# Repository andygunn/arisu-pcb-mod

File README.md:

# Arisu Keyboard PCB with Modifications
アリス PCB designed using KiCad. The layout was originally created by FateNozomi, inspired by Lyn's EM7 and TGR Alice with some modification.

Key differences of the original PCB:
- Removed the extra [B] key on the right half and shifted the [NM,.?] row to the left by 0.25U.
- Shifted the 3 keys to the right and added arrow keys.
- Tweaked the bottom so that the 1.5U keys doesn't protrude out a little.

Additional modifications to the file include:
- Addition of stepped capslock position.
- Addition of full backspace position, connected to switch 59 (row 0, column 13).
- Replacing the mini-USB connector with USB-C.
- Shifting the USB-C connector vertically, to reduce the distance to the edge of a case.

(Note: The modifications for full backspace and stepped capslock require a modification to the plate file to use.)

Shifting the [NM,.?] row to the left by 0.25U required quite some work on the arrangement of keys for the right half.
As a result, this does not give the same typing experience as Lyn's EM7 and TGR Alice.
Lyn's EM7 and TGR Alice uses the home row as the center point to vertically align both halves while I used the number row instead.
Due to the nature of staggered keyboards, aligning using the number row resulted in the home row not being aligned.

Disclaimer: Use these files at your own risk.

## Gerber Files
Download the gerber files under [releases](https://github.com/andygunn/arisu-pcb-mod/releases).

## Assembly
For the components required, you may refer to the bill of materials included along with the release as reference or load up the design file in KiCad.
All the components can be soldered using a regular soldering iron, though soldering the Micro USB receptacle might be the biggest hurdle.

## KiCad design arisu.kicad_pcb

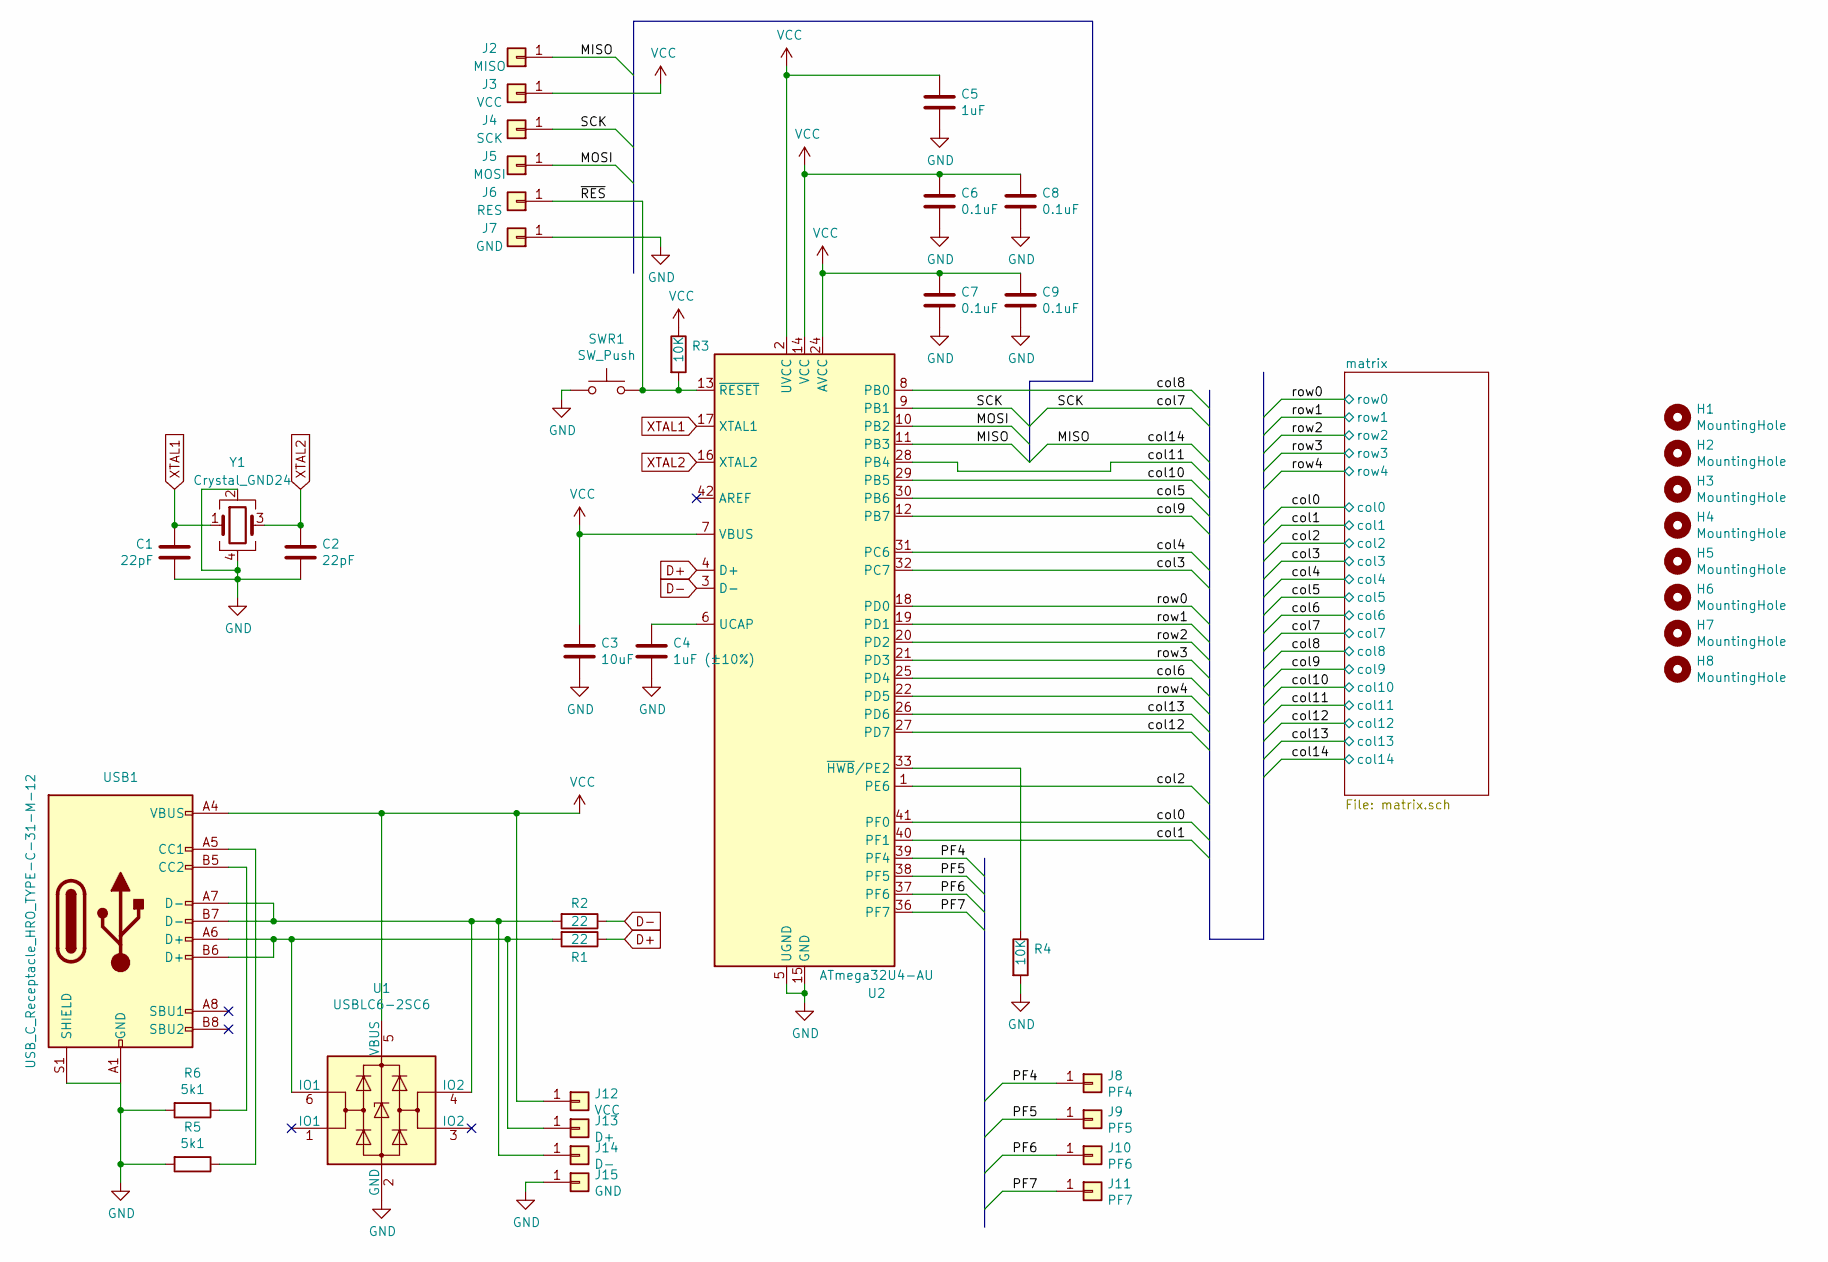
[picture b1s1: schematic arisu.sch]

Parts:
C1, C2: 22pF; C_0805_HandSoldering; LCSC C1804
C3: 10uF; C_0805_HandSoldering; LCSC C15850
C4: 1uF (±10%); C_0805_HandSoldering; LCSC C28323
C5: 1uF; C_0805_HandSoldering; LCSC C28323
C6, C7, C8, C9: 0.1uF; C_0805_HandSoldering; LCSC C28233
H1, H2, H3, H4, H5, H6, H7, H8: MountingHole; MountingHole_2.2mm_M2_Pad
J2: MISO; Pin_Header_Straight_1x01_Pitch2.54mm
J3, J12: VCC; Pin_Header_Straight_1x01_Pitch2.54mm
J4: SCK; Pin_Header_Straight_1x01_Pitch2.54mm
J5: MOSI; Pin_Header_Straight_1x01_Pitch2.54mm
J6: RES; Pin_Header_Straight_1x01_Pitch2.54mm
J7, J15: GND; Pin_Header_Straight_1x01_Pitch2.54mm
J8: PF4; Pin_Header_Straight_1x01_Pitch2.54mm
J9: PF5; Pin_Header_Straight_1x01_Pitch2.54mm
J10: PF6; Pin_Header_Straight_1x01_Pitch2.54mm
J11: PF7; Pin_Header_Straight_1x01_Pitch2.54mm
J13: D+; Pin_Header_Straight_1x01_Pitch2.54mm
J14: D-; Pin_Header_Straight_1x01_Pitch2.54mm
R1, R2: 22; R_0805_HandSoldering; LCSC C17561
R3, R4: 10K; R_0805_HandSoldering; LCSC C17414
R5, R6: 5k1; R_0805_2012Metric_Pad1.15x1.40mm_HandSolder; LCSC C27834
SWR1: SW_Push; SW_SPST_TL3342; LCSC C318884
U1: USBLC6-2SC6; SOT-23-6_Handsoldering; LCSC C7519
U2: ATmega32U4-AU; TQFP-44_10x10mm_P0.8mm; LCSC C44854
USB1: USB_C_Receptacle_HRO_TYPE-C-31-M-12
Y1: Crystal_GND24; Crystal_SMD_SeikoEpson_FA238-4pin_3.2x2.5mm_HandSoldering; LCSC C89371

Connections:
/MISO: J2.1, U2.11 (PB3); also elsewhere on the board
/MOSI: J5.1, U2.10 (PB2)
/PF4: J8.1, U2.39 (PF4)
/PF5: J9.1, U2.38 (PF5)
/PF6: J10.1, U2.37 (PF6)
/PF7: J11.1, U2.36 (PF7)
/SCK: J4.1, U2.9 (PB1); also elsewhere on the board
/col0: U2.41 (PF0); also elsewhere on the board
/col1: U2.40 (PF1); also elsewhere on the board
/col2: U2.1 (PE6); also elsewhere on the board
/col3: U2.32 (PC7); also elsewhere on the board
/col4: U2.31 (PC6); also elsewhere on the board
/col5: U2.30 (PB6); also elsewhere on the board
/col6: U2.25 (PD4); also elsewhere on the board
/col8: U2.8 (PB0); also elsewhere on the board
/col9: U2.12 (PB7); also elsewhere on the board
/col10: U2.29 (PB5); also elsewhere on the board
/col11: U2.28 (PB4); also elsewhere on the board
/col12: U2.27 (PD7); also elsewhere on the board
/col13: U2.26 (PD6); also elsewhere on the board
/row0: U2.18 (PD0); also elsewhere on the board
/row1: U2.19 (PD1); also elsewhere on the board
/row2: U2.20 (PD2); also elsewhere on the board
/row3: U2.21 (PD3); also elsewhere on the board
/row4: U2.22 (PD5); also elsewhere on the board
/~RES~: J6.1, R3.2, SWR1.2, U2.13 (~RESET)
D+: R1.1, U2.4 (D+)
D-: R2.1, U2.3 (D-)
GND: C1.1, C2.2, C3.2, C4.2, C5.2, C6.2, C7.2, C8.2, C9.2, J7.1, J15.1, R4.2, R5.2, R6.2, SWR1.1, U1.2 (GND), U2.5 (UGND), U2.15 (GND), U2.23 (GND), U2.35 (GND), U2.43 (GND), USB1.A1 (GND), USB1.A12 (GND), USB1.S1 (SHIELD), Y1.2, Y1.4
unnamed: C4.1, U2.6 (UCAP)
unnamed: J13.1, R1.2, U1.6 (IO1), USB1.A6 (D+), USB1.B6 (D+)
unnamed: J14.1, R2.2, U1.4 (IO2), USB1.A7 (D-), USB1.B7 (D-)
unnamed: R4.1, U2.33 (~HWB~/PE2)
unnamed: R5.1, USB1.A5 (CC1)
unnamed: R6.1, USB1.B5 (CC2)
VCC: C3.1, C5.1, C6.1, C7.1, C8.1, C9.1, J3.1, J12.1, R3.1, U1.5 (VBUS), U2.2 (UVCC), U2.7 (VBUS), U2.14 (VCC), U2.24 (AVCC), U2.34 (VCC), U2.44 (AVCC), USB1.A4 (VBUS), USB1.A9 (VBUS)
XTAL1: C1.2, U2.17 (XTAL1), Y1.1
XTAL2: C2.1, U2.16 (XTAL2), Y1.3

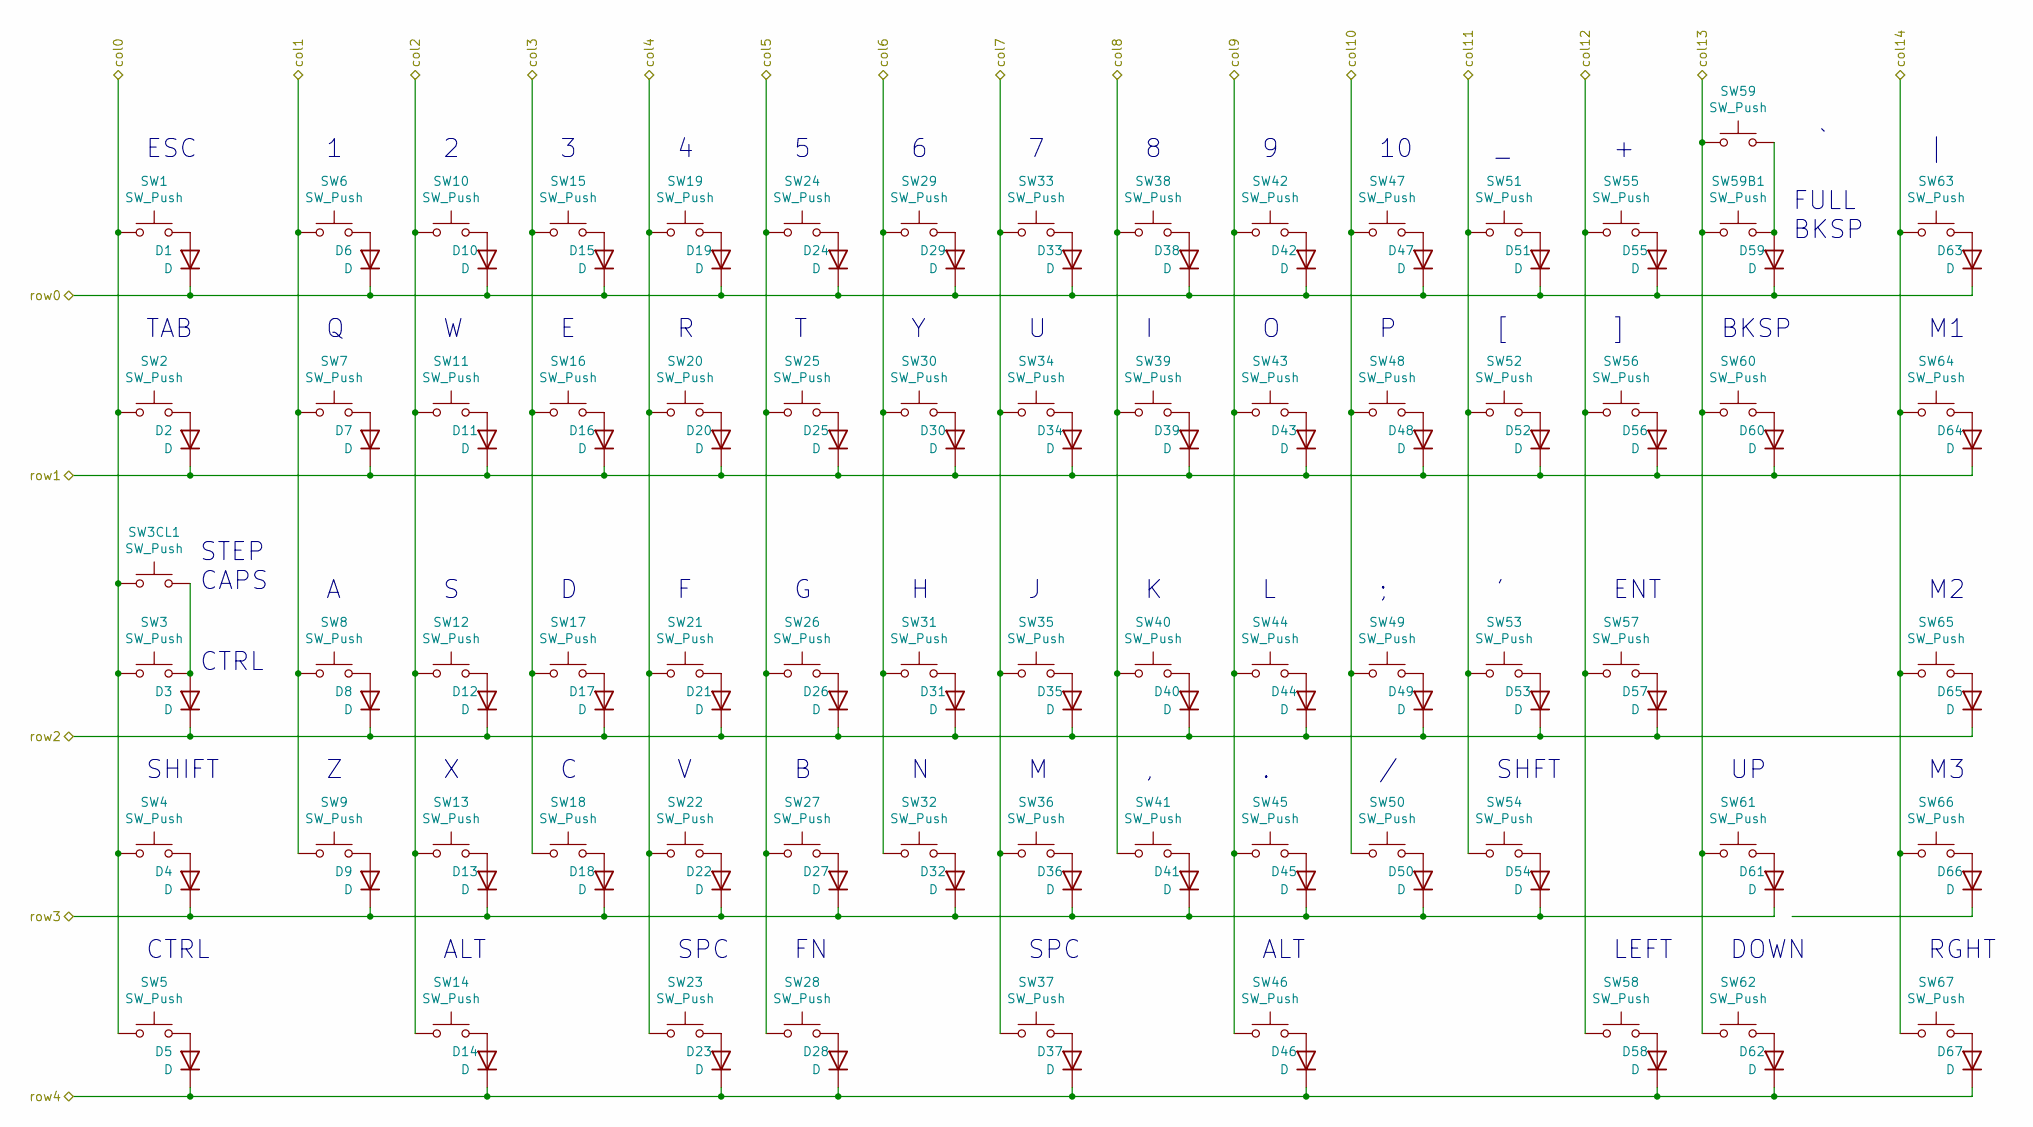
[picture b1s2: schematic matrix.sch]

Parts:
D1, D2, D3, D4, D5, D6, D7, D8, D9, D10, D11, D12, D13, D14, D15, D16, D17, D18, D19, D20, D21, D22, D23, D24, D25, D26, D27, D28, D29, D30, D31, D32, D33, D34, D35, D36, D37, D38, D39, D40, D41, D42, D43, D44, D45, D46, D47, D48, D49, D50, D51, D52, D53, D54, D55, D56, D57, D58, D59, D60, D61, D62, D63, D64, D65, D66, D67: D; D_SOD-123; LCSC C81598
SW1, SW6, SW7, SW8, SW9, SW10, SW11, SW12, SW13, SW15, SW16, SW17, SW18, SW19, SW20, SW21, SW22, SW24, SW25, SW26, SW27, SW28, SW29, SW30, SW31, SW32, SW33, SW34, SW35, SW36, SW38, SW39, SW40, SW41, SW42, SW43, SW44, SW45, SW47, SW48, SW49, SW50, SW51, SW52, SW53, SW55, SW56, SW58, SW59, SW61, SW62, SW63, SW64, SW65, SW66, SW67: SW_Push; SW_Cherry_MX_1.00u_PCB
SW2, SW5, SW14, SW46, SW60: SW_Push; SW_Cherry_MX_1.50u_PCB
SW3, SW54: SW_Push; SW_Cherry_MX_1.75u_PCB
SW3CL1: SW_Push; SW_Cherry_MX_1.25u_PCB
SW4: SW_Push; SW_Cherry_MX_2.25u_PCB
SW23: SW_Push; SW_Cherry_MX_2.00u_PCB_ReversedStabilizers
SW37: SW_Push; SW_Cherry_MX_2.75u_PCB_ReversedStabilizers
SW57: SW_Push; SW_Cherry_MX_2.25u_PCB_ReversedStabilizers
SW59B1: SW_Push; SW_Cherry_MX_2.00u_PCB

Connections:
/MISO: SW63.1, SW64.1, SW65.1, SW66.1, SW67.1; also elsewhere on the board
/SCK: SW33.1, SW34.1, SW35.1, SW36.1, SW37.1; also elsewhere on the board
/col0: SW1.1, SW2.1, SW3.1, SW3CL1.1, SW4.1, SW5.1; also elsewhere on the board
/col1: SW6.1, SW7.1, SW8.1, SW9.1; also elsewhere on the board
/col2: SW10.1, SW11.1, SW12.1, SW13.1, SW14.1; also elsewhere on the board
/col3: SW15.1, SW16.1, SW17.1, SW18.1; also elsewhere on the board
/col4: SW19.1, SW20.1, SW21.1, SW22.1, SW23.1; also elsewhere on the board
/col5: SW24.1, SW25.1, SW26.1, SW27.1, SW28.1; also elsewhere on the board
/col6: SW29.1, SW30.1, SW31.1, SW32.1; also elsewhere on the board
/col8: SW38.1, SW39.1, SW40.1, SW41.1; also elsewhere on the board
/col9: SW42.1, SW43.1, SW44.1, SW45.1, SW46.1; also elsewhere on the board
/col10: SW47.1, SW48.1, SW49.1, SW50.1; also elsewhere on the board
/col11: SW51.1, SW52.1, SW53.1, SW54.1; also elsewhere on the board
/col12: SW55.1, SW56.1, SW57.1, SW58.1; also elsewhere on the board
/col13: SW59.1, SW59B1.1, SW60.1, SW61.1, SW62.1; also elsewhere on the board
/row0: D1.1 (K), D6.1 (K), D10.1 (K), D15.1 (K), D19.1 (K), D24.1 (K), D29.1 (K), D33.1 (K), D38.1 (K), D42.1 (K), D47.1 (K), D51.1 (K), D55.1 (K), D59.1 (K), D63.1 (K); also elsewhere on the board
/row1: D2.1 (K), D7.1 (K), D11.1 (K), D16.1 (K), D20.1 (K), D25.1 (K), D30.1 (K), D34.1 (K), D39.1 (K), D43.1 (K), D48.1 (K), D52.1 (K), D56.1 (K), D60.1 (K), D64.1 (K); also elsewhere on the board
/row2: D3.1 (K), D8.1 (K), D12.1 (K), D17.1 (K), D21.1 (K), D26.1 (K), D31.1 (K), D35.1 (K), D40.1 (K), D44.1 (K), D49.1 (K), D53.1 (K), D57.1 (K), D65.1 (K); also elsewhere on the board
/row3: D4.1 (K), D9.1 (K), D13.1 (K), D18.1 (K), D22.1 (K), D27.1 (K), D32.1 (K), D36.1 (K), D41.1 (K), D45.1 (K), D50.1 (K), D54.1 (K), D61.1 (K); also elsewhere on the board
/row4: D5.1 (K), D14.1 (K), D23.1 (K), D28.1 (K), D37.1 (K), D46.1 (K), D58.1 (K), D62.1 (K), D67.1 (K); also elsewhere on the board
unnamed: D1.2 (A), SW1.2
unnamed: D2.2 (A), SW2.2
unnamed: D3.2 (A), SW3.2, SW3CL1.2
unnamed: D4.2 (A), SW4.2
unnamed: D5.2 (A), SW5.2
unnamed: D6.2 (A), SW6.2
unnamed: D7.2 (A), SW7.2
unnamed: D8.2 (A), SW8.2
unnamed: D9.2 (A), SW9.2
unnamed: D10.2 (A), SW10.2
unnamed: D11.2 (A), SW11.2
unnamed: D12.2 (A), SW12.2
unnamed: D13.2 (A), SW13.2
unnamed: D14.2 (A), SW14.2
unnamed: D15.2 (A), SW15.2
unnamed: D16.2 (A), SW16.2
unnamed: D17.2 (A), SW17.2
unnamed: D18.2 (A), SW18.2
unnamed: D19.2 (A), SW19.2
unnamed: D20.2 (A), SW20.2
unnamed: D21.2 (A), SW21.2
unnamed: D22.2 (A), SW22.2
unnamed: D23.2 (A), SW23.2
unnamed: D24.2 (A), SW24.2
unnamed: D25.2 (A), SW25.2
unnamed: D26.2 (A), SW26.2
unnamed: D27.2 (A), SW27.2
unnamed: D28.2 (A), SW28.2
unnamed: D29.2 (A), SW29.2
unnamed: D30.2 (A), SW30.2
unnamed: D31.2 (A), SW31.2
unnamed: D32.2 (A), SW32.2
unnamed: D33.2 (A), SW33.2
unnamed: D34.2 (A), SW34.2
unnamed: D35.2 (A), SW35.2
unnamed: D36.2 (A), SW36.2
unnamed: D37.2 (A), SW37.2
unnamed: D38.2 (A), SW38.2
unnamed: D39.2 (A), SW39.2
unnamed: D40.2 (A), SW40.2
unnamed: D41.2 (A), SW41.2
unnamed: D42.2 (A), SW42.2
unnamed: D43.2 (A), SW43.2
unnamed: D44.2 (A), SW44.2
unnamed: D45.2 (A), SW45.2
unnamed: D46.2 (A), SW46.2
unnamed: D47.2 (A), SW47.2
unnamed: D48.2 (A), SW48.2
unnamed: D49.2 (A), SW49.2
unnamed: D50.2 (A), SW50.2
unnamed: D51.2 (A), SW51.2
unnamed: D52.2 (A), SW52.2
unnamed: D53.2 (A), SW53.2
unnamed: D54.2 (A), SW54.2
unnamed: D55.2 (A), SW55.2
unnamed: D56.2 (A), SW56.2
unnamed: D57.2 (A), SW57.2
unnamed: D58.2 (A), SW58.2
unnamed: D59.2 (A), SW59.2, SW59B1.2
unnamed: D60.2 (A), SW60.2
unnamed: D61.2 (A), SW61.2
unnamed: D62.2 (A), SW62.2
unnamed: D63.2 (A), SW63.2
unnamed: D64.2 (A), SW64.2
unnamed: D65.2 (A), SW65.2
unnamed: D66.2 (A), SW66.2
unnamed: D67.2 (A), SW67.2

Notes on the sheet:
ESC
TAB
BKSP
CTRL
ENT
RGHT
LEFT
DOWN
SPC
ALT
SHFT
SHIFT
FULL BKSP
STEP CAPS

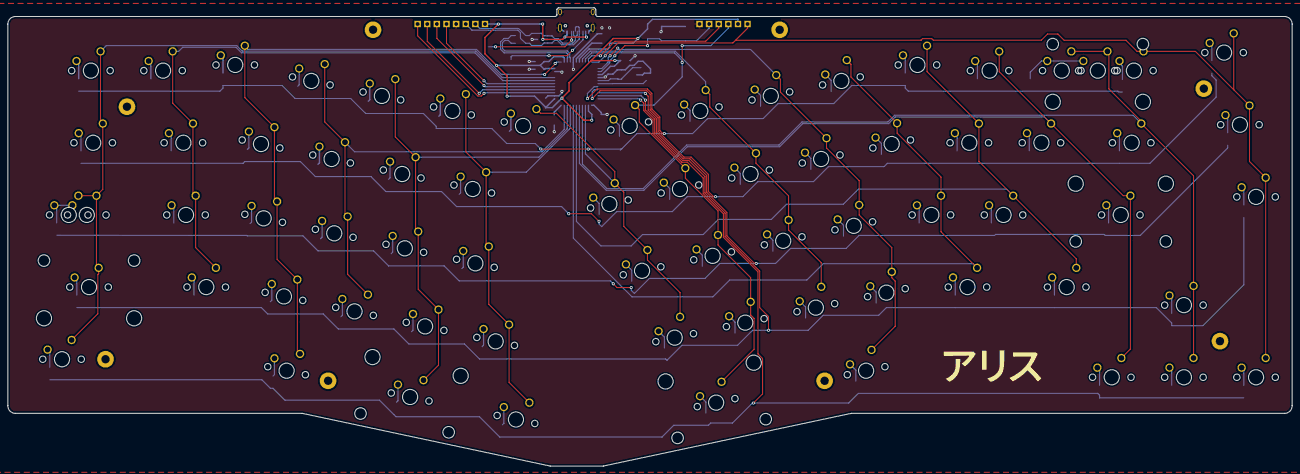
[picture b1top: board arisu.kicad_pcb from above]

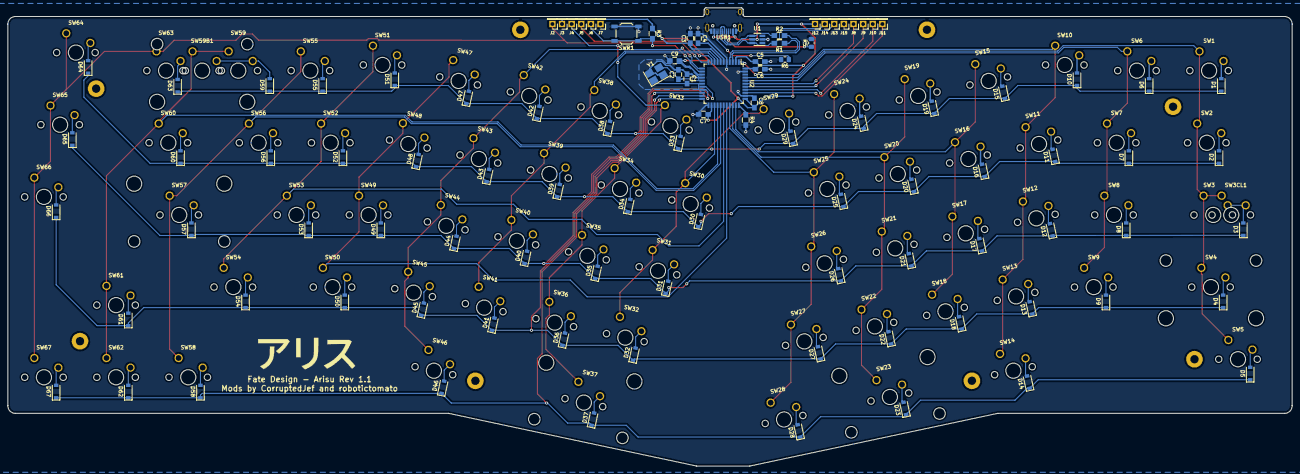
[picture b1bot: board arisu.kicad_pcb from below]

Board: 2 copper layers, 339.1 x 121.0 mm, 178 parts (101 on the bottom side), 105 nets.

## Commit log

2020-10-20 Initial project update
    - Imported FateParts library
    - Updated schematic with full backspace switch and stepped capslock switch
    - Added new switch footprints to layout
    - Updated some traces in layout
2020-10-21 Changed mini-USB to USB-C
    - Removed mini-USB from schematic and layout
    - Added USB-C to schematic and layout
    - Added 5k1 resistors for CC1 and CC2 pins, added to layout
    - Added bump-out on PCB for USB-C connector to protrude slightly
    - Rerouted traces as necessary
2020-10-21 Additional trace cleanup
    Some more trace cleanup for the USB data lines from the connector.
2020-10-22 Addition of BOM and position files
    - Added JLCPCB part numbers in BOM and exported
    - Exported component positioning file
    - Some minor cleanup of traces and silkscreen legend positions.
2020-10-29 Create arisu-full-backspace.json
    Added testing .json file for use with Via - will need to be manually loaded, but allows for "Full Backspace" view while testing.
2020-12-09 Add submodules for Fate Parts
2020-12-09 Small cleanup and updates
